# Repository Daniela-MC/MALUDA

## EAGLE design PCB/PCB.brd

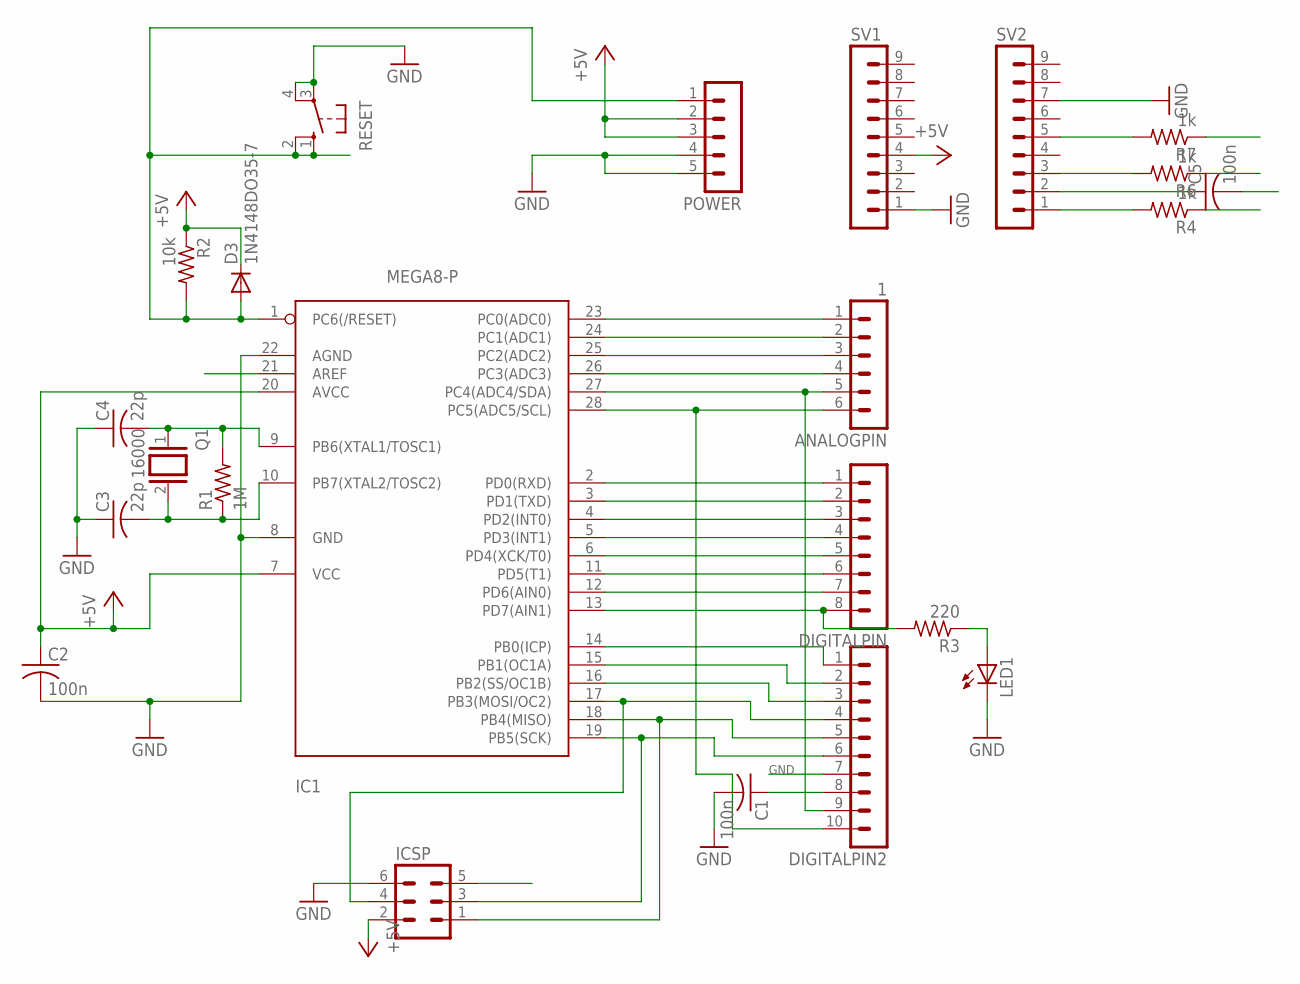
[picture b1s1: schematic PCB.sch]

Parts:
ANALOGPIN: 1; MA06-1
C1, C2, C5: 100n; C025-024X044
C3, C4: 22p; C025-024X044
D3: 1N4148DO35-7; DO35-7
DIGITALPIN: MA08-1
DIGITALPIN2: MA10-1
IC1: MEGA8-P; DIL28-3
ICSP: MA03-2
LED1: LED3MM
POWER: MA05-1
Q1: 16000; QS
R1: 1M; 0204/7
R2: 10k; 0204/7
R3: 220; 0204/7
R4, R6, R7: 1k; 0204/7
RESET: 10-XX; B3F-10XX
SV1, SV2: MA09-1

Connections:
+5V: C2.1, D3.C, IC1.7 (VCC), IC1.20 (AVCC), ICSP.2, POWER.2, POWER.3, R2.1, SV1.4
AREF: C1.1, DIGITALPIN2.8, IC1.21 (AREF)
GND: C1.2, C2.2, C3.1, C4.1, DIGITALPIN2.7, IC1.8 (GND), IC1.22 (AGND), ICSP.6, LED1.K (C), POWER.4, POWER.5, RESET.3, RESET.4 (P1), SV1.1, SV2.7
unnamed: C4.2, IC1.9 (PB6(XTAL1/TOSC1)), Q1.1, R1.2
unnamed: C3.2, IC1.10 (PB7(XTAL2/TOSC2)), Q1.2, R1.1
unnamed: LED1.A, R3.1
unnamed: C5.1, SV2.2
unnamed: R7.2, SV2.5
unnamed: DIGITALPIN.3, IC1.4 (PD2(INT0))
unnamed: DIGITALPIN.4, IC1.5 (PD3(INT1))
unnamed: DIGITALPIN.5, IC1.6 (PD4(XCK/T0))
unnamed: DIGITALPIN.6, IC1.11 (PD5(T1))
unnamed: DIGITALPIN.7, IC1.12 (PD6(AIN0))
unnamed: DIGITALPIN.8, IC1.13 (PD7(AIN1)), R3.2
unnamed: ANALOGPIN.1, IC1.23 (PC0(ADC0))
unnamed: ANALOGPIN.2, IC1.24 (PC1(ADC1))
unnamed: ANALOGPIN.3, IC1.25 (PC2(ADC2))
unnamed: ANALOGPIN.4, IC1.26 (PC3(ADC3))
unnamed: ANALOGPIN.5, DIGITALPIN2.9, IC1.27 (PC4(ADC4/SDA))
unnamed: R4.2, SV2.1
unnamed: DIGITALPIN2.1, IC1.14 (PB0(ICP))
unnamed: DIGITALPIN2.2, IC1.15 (PB1(OC1A))
unnamed: DIGITALPIN2.3, IC1.16 (PB2(SS/OC1B))
unnamed: DIGITALPIN2.5, IC1.18 (PB4(MISO)), ICSP.1
unnamed: DIGITALPIN2.6, IC1.19 (PB5(SCK)), ICSP.3
unnamed: R6.2, SV2.3
unnamed: DIGITALPIN2.4, IC1.17 (PB3(MOSI/OC2)), ICSP.4
unnamed: ANALOGPIN.6, DIGITALPIN2.10, IC1.28 (PC5(ADC5/SCL))
RES1: C5.2, D3.A, IC1.1 (PC6(/RESET)), ICSP.5, POWER.1, R2.2, R6.1, RESET.1 (S), RESET.2 (S1)
RXD: DIGITALPIN.1, IC1.2 (PD0(RXD)), R4.1
TXD: DIGITALPIN.2, IC1.3 (PD1(TXD)), R7.1

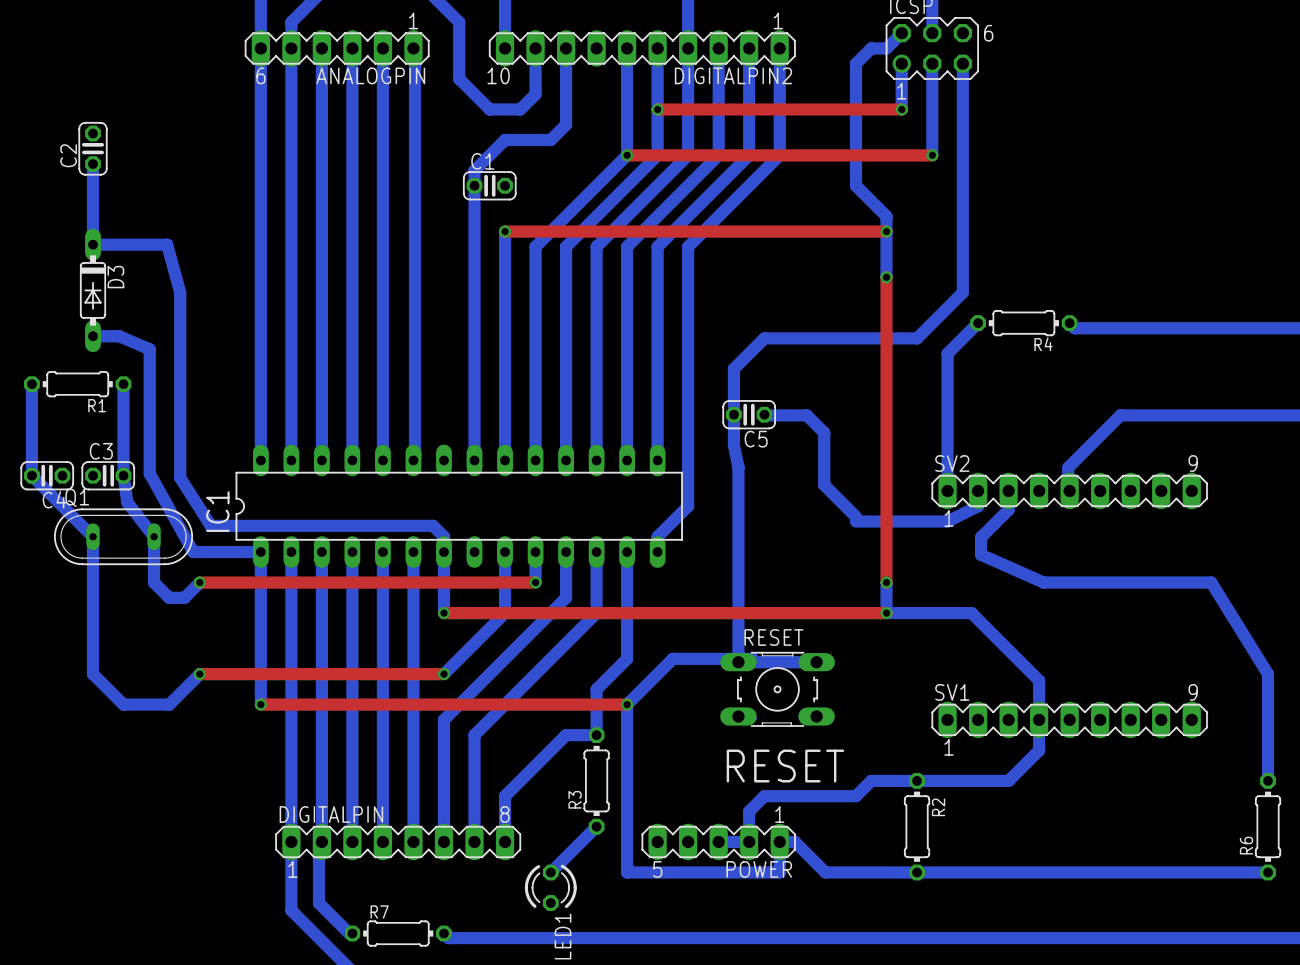
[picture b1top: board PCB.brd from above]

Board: 2 copper layers, 23 parts (0 on the bottom side), 31 nets.

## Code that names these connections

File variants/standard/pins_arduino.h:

/*
  pins_arduino.h - Pin definition functions for Arduino
  Part of Arduino - http://www.arduino.cc/

  Copyright (c) 2007 David A. Mellis

  This library is free software; you can redistribute it and/or
  modify it under the terms of the GNU Lesser General Public
  License as published by the Free Software Foundation; either
  version 2.1 of the License, or (at your option) any later version.

  This library is distributed in the hope that it will be useful,
  but WITHOUT ANY WARRANTY; without even the implied warranty of
  MERCHANTABILITY or FITNESS FOR A PARTICULAR PURPOSE.  See the GNU
  Lesser General Public License for more details.

  You should have received a copy of the GNU Lesser General
  Public License along with this library; if not, write to the
  Free Software Foundation, Inc., 59 Temple Place, Suite 330,
  Boston, MA  02111-1307  USA
*/

#ifndef Pins_Arduino_h
#define Pins_Arduino_h

#include <avr/pgmspace.h>

#define NUM_DIGITAL_PINS            20
#define NUM_ANALOG_INPUTS           6
#define analogInputToDigitalPin(p)  ((p < 6) ? (p) + 14 : -1)

#if defined(__AVR_ATmega8__)
#define digitalPinHasPWM(p)         ((p) == 9 || (p) == 10 || (p) == 11)
#else
#define digitalPinHasPWM(p)         ((p) == 3 || (p) == 5 || (p) == 6 || (p) == 9 || (p) == 10 || (p) == 11)
#endif

#define PIN_SPI_SS    (10)
#define PIN_SPI_MOSI  (11)
#define PIN_SPI_MISO  (12)
#define PIN_SPI_SCK   (13)

static const uint8_t SS   = PIN_SPI_SS;
static const uint8_t MOSI = PIN_SPI_MOSI;
static const uint8_t MISO = PIN_SPI_MISO;
static const uint8_t SCK  = PIN_SPI_SCK;

#define PIN_WIRE_SDA        (18)
#define PIN_WIRE_SCL        (19)

static const uint8_t SDA = PIN_WIRE_SDA;
static const uint8_t SCL = PIN_WIRE_SCL;

#define LED_BUILTIN 7

#define PIN_A0   (14)
#define PIN_A1   (15)
#define PIN_A2   (16)
#define PIN_A3   (17)
#define PIN_A4   (18)
#define PIN_A5   (19)
#define PIN_A6   (20)
#define PIN_A7   (21)

static const uint8_t A0 = PIN_A0;
static const uint8_t A1 = PIN_A1;
static const uint8_t A2 = PIN_A2;
static const uint8_t A3 = PIN_A3;
static const uint8_t A4 = PIN_A4;
static const uint8_t A5 = PIN_A5;
static const uint8_t A6 = PIN_A6;
static const uint8_t A7 = PIN_A7;

#define digitalPinToPCICR(p)    (((p) >= 0 && (p) <= 21) ? (&PCICR) : ((uint8_t *)0))
#define digitalPinToPCICRbit(p) (((p) <= 7) ? 2 : (((p) <= 13) ? 0 : 1))
#define digitalPinToPCMSK(p)    (((p) <= 7) ? (&PCMSK2) : (((p) <= 13) ? (&PCMSK0) : (((p) <= 21) ? (&PCMSK1) : ((uint8_t *)0))))
#define digitalPinToPCMSKbit(p) (((p) <= 7) ? (p) : (((p) <= 13) ? ((p) - 8) : ((p) - 14)))

#define digitalPinToInterrupt(p)  ((p) == 2 ? 0 : ((p) == 3 ? 1 : NOT_AN_INTERRUPT))

#ifdef ARDUINO_MAIN

// On the Arduino board, digital pins are also used
// for the analog output (software PWM).  Analog input
// pins are a separate set.

// ATMEL ATMEGA8 & 168 / ARDUINO
//
//                  +-\/-+
//            PC6  1|    |28  PC5 (AI 5)
//      (D 0) PD0  2|    |27  PC4 (AI 4)
//      (D 1) PD1  3|    |26  PC3 (AI 3)
//      (D 2) PD2  4|    |25  PC2 (AI 2)
// PWM+ (D 3) PD3  5|    |24  PC1 (AI 1)
//      (D 4) PD4  6|    |23  PC0 (AI 0)
//            VCC  7|    |22  GND
//            GND  8|    |21  AREF
//            PB6  9|    |20  AVCC
//            PB7 10|    |19  PB5 (D 13)
// PWM+ (D 5) PD5 11|    |18  PB4 (D 12)
// PWM+ (D 6) PD6 12|    |17  PB3 (D 11) PWM
//      (D 7) PD7 13|    |16  PB2 (D 10) PWM
//      (D 8) PB0 14|    |15  PB1 (D 9) PWM
//                  +----+
//
// (PWM+ indicates the additional PWM pins on the ATmega168.)

// ATMEL ATMEGA1280 / ARDUINO
//
// 0-7 PE0-PE7   works
// 8-13 PB0-PB5  works
// 14-21 PA0-PA7 works
// 22-29 PH0-PH7 works
// 30-35 PG5-PG0 works
// 36-43 PC7-PC0 works
// 44-51 PJ7-PJ0 works
// 52-59 PL7-PL0 works
// 60-67 PD7-PD0 works
// A0-A7 PF0-PF7
// A8-A15 PK0-PK7


// these arrays map port names (e.g. port B) to the
// appropriate addresses for various functions (e.g. reading
// and writing)
const uint16_t PROGMEM port_to_mode_PGM[] = {
	NOT_A_PORT,
	NOT_A_PORT,
	(uint16_t) &DDRB,
	(uint16_t) &DDRC,
	(uint16_t) &DDRD,
};

const uint16_t PROGMEM port_to_output_PGM[] = {
	NOT_A_PORT,
	NOT_A_PORT,
	(uint16_t) &PORTB,
	(uint16_t) &PORTC,
	(uint16_t) &PORTD,
};

const uint16_t PROGMEM port_to_input_PGM[] = {
	NOT_A_PORT,
	NOT_A_PORT,
	(uint16_t) &PINB,
	(uint16_t) &PINC,
	(uint16_t) &PIND,
};

const uint8_t PROGMEM digital_pin_to_port_PGM[] = {
	PD, /* 0 */
	PD,//iguales
	PB,
	PB,
	PB,
	PB,
	PD,
	PB,
	PD, /* 8 */
	PD,
	PD,
	PD,
	PD,
	PD,
	PC, /* 14 */
	PC,
	PC,
	PC,
	PC,
	PC,
};

const uint8_t PROGMEM digital_pin_to_bit_mask_PGM[] = {
	_BV(0), /* 0, port D */
	_BV(1),
	_BV(0),
	_BV(1),
	_BV(2),
	_BV(3),
	_BV(4),
	_BV(5),
	_BV(2), /* 8, port B */
	_BV(3),
	_BV(4),
	_BV(5),
	_BV(6),
	_BV(7),
	_BV(0), /* 14, port C */
	_BV(1),
	_BV(2),
	_BV(3),
	_BV(4),
	_BV(5),
};

const uint8_t PROGMEM digital_pin_to_timer_PGM[] = {
	NOT_ON_TIMER, /* 0 - port D */
	NOT_ON_TIMER,
	NOT_ON_TIMER,
	// on the ATmega168, digital pin 3 has hardware pwm
#if defined(__AVR_ATmega8__)
	NOT_ON_TIMER,
#else
	TIMER2B,
#endif
	NOT_ON_TIMER,
	// on the ATmega168, digital pins 5 and 6 have hardware pwm
#if defined(__AVR_ATmega8__)
	NOT_ON_TIMER,
	NOT_ON_TIMER,
#else
	TIMER0B,
	TIMER0A,
#endif
	NOT_ON_TIMER,
	NOT_ON_TIMER, /* 8 - port B */
	TIMER1A,
	TIMER1B,
#if defined(__AVR_ATmega8__)
	TIMER2,
#else
	TIMER2A,
#endif
	NOT_ON_TIMER,
	NOT_ON_TIMER,
	NOT_ON_TIMER,
	NOT_ON_TIMER, /* 14 - port C */
	NOT_ON_TIMER,
	NOT_ON_TIMER,
	NOT_ON_TIMER,
	NOT_ON_TIMER,
};

#endif

// These serial port names are intended to allow libraries and architecture-neutral
// sketches to automatically default to the correct port name for a particular type
// of use.  For example, a GPS module would normally connect to SERIAL_PORT_HARDWARE_OPEN,
// the first hardware serial port whose RX/TX pins are not dedicated to another use.
//
// SERIAL_PORT_MONITOR        Port which normally prints to the Arduino Serial Monitor
//
// SERIAL_PORT_USBVIRTUAL     Port which is USB virtual serial
//
// SERIAL_PORT_LINUXBRIDGE    Port which connects to a Linux system via Bridge library
//
// SERIAL_PORT_HARDWARE       Hardware serial port, physical RX & TX pins.
//
// SERIAL_PORT_HARDWARE_OPEN  Hardware serial ports which are open for use.  Their RX & TX
//                            pins are NOT connected to anything by default.
#define SERIAL_PORT_MONITOR   Serial
#define SERIAL_PORT_HARDWARE  Serial

#endif

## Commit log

2017-02-20 imagen del diseño
2017-02-21 -Archivo json
2017-02-21 archivo json
2017-02-24 se agrega la carpeta Avr
2017-02-24 v0.1.0
2017-02-24 Se agregó la carpeta avr
2017-02-27 Diseño del PCB
2017-03-07 circuito impreso MALUDA
2017-03-07 diseño final del PCB
2017-03-13 nueva version cambio de pines
2017-03-13 versión v0.1.1
2017-03-13 New version
2017-03-31 cambio de las veces que enciende el led
2017-03-31 vo.1.2
